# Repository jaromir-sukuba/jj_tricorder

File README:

This is repository for JJ Tricorder project, hosted here http://hackaday.io/project/521-JJ-Tricoder

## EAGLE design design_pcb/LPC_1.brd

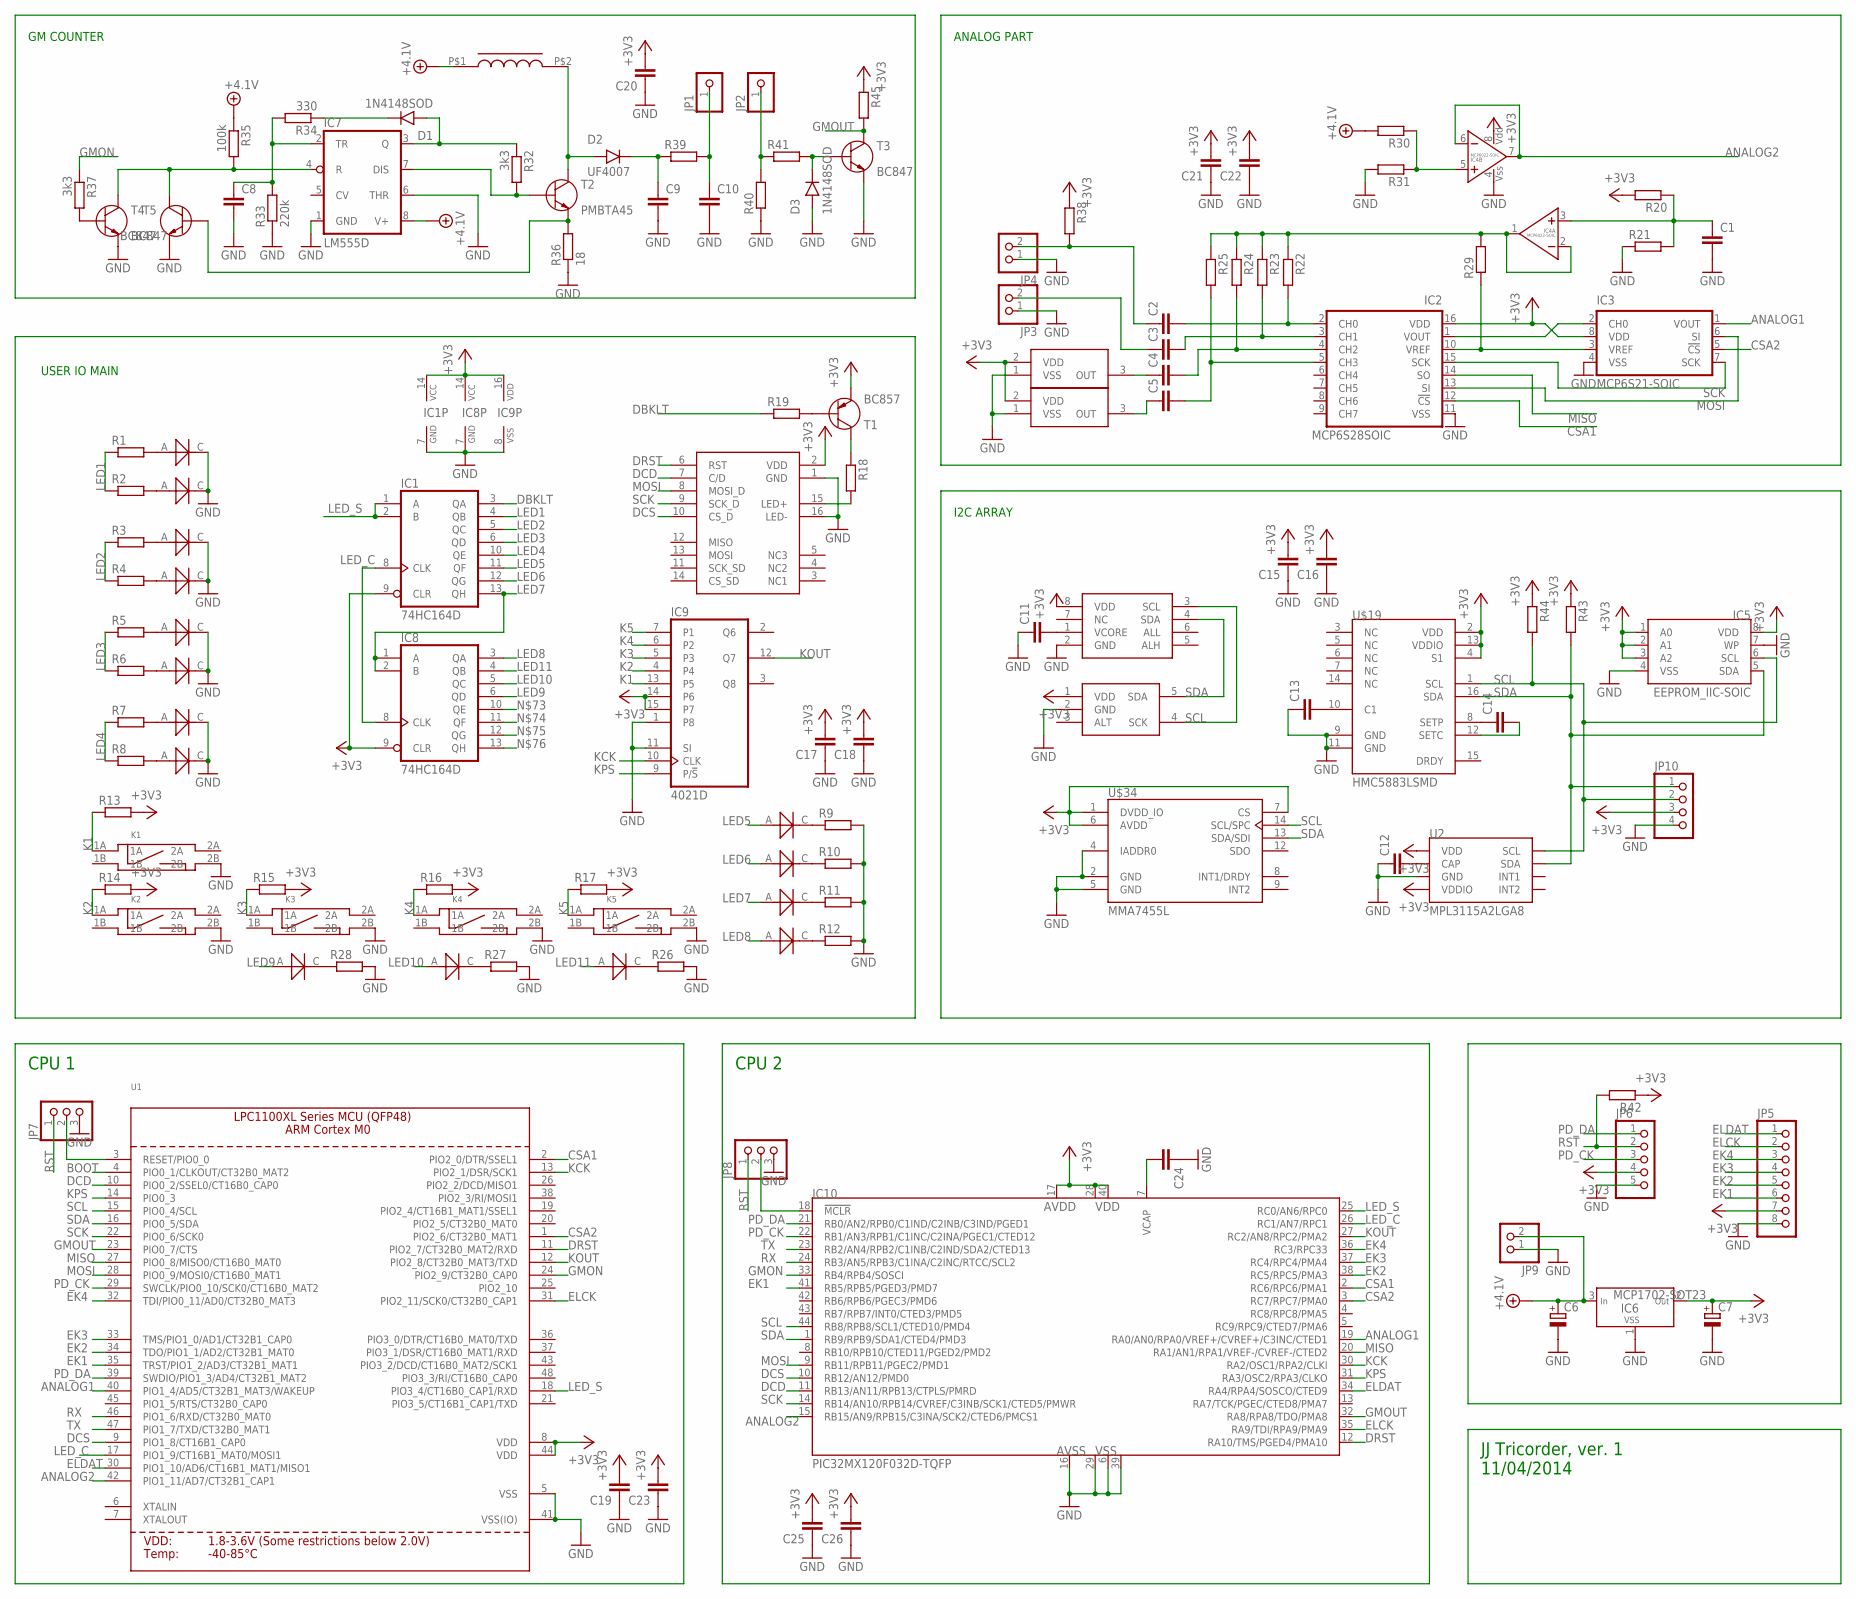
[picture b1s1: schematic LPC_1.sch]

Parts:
C1, C8, C11, C12, C13, C14, C15, C16, C17, C18, C19, C20, C21, C22, C23, C24, C25, C26: C_0806; R0805
C2, C3, C4, C5, C9, C10: C_1206; R1206
C6, C7: CPOL-EUSMCA; SMC_A
D1, D3: 1N4148SOD; SOD-80
D2: UF4007; SM-1
IC1, IC8: 74HC164D; SO14
IC2: MCP6S28SOIC; SO-16
IC3: MCP6S21-SOIC; SO-08
IC4: MCP6022-SOIC; SO-08
IC5: EEPROM_IIC-SOIC; SO-08
IC6: MCP1702-SOT23; SOT23
IC7: LM555D; SO08
IC9: 4021D; SO16
IC10: PIC32MX120F032D-TQFP; TQFP44
JP1, JP2: PINHD-1X1; 1X01
JP3, JP4: PINHD-1X02_2.54; 1X02
JP5: PINHD-1X08_2.54-S; 1X08-S
JP6: PINHD-1X05_2.54-90°-S; 1X05/90-S
JP7, JP8: PINHD-1X03_2.00; 1X03M
JP9: PINHD-1X02_2.54-90°; 1X02/90
JP10: PINHD-1X04_2.00; 1X04M
K1, K2, K3, K4, K5: SWITCH_BD_B; SW_SMD2
R1, R2, R3, R4, R5, R6, R7, R8, R9, R10, R11, R12, R13, R14, R15, R16, R17, R18, R19, R20, R21, R22, R23, R24, R25, R26, R27, R28, R29, R30, R31, R38, R41, R42, R43, R44, R45: R_0805; R0805
R32, R37: 3k3; R0805
R33: 220k; R0805
R34: 330; R0805
R35: 100k; R0805
R36: 18; R0805
R39, R40: R_1206; R1206
T1: BC857; SOT23
T2: PMBTA45; SOT23
T3, T4, T5: BC847; SOT23
U1: LPC1113/4/5_QFP48_XLSERIES; LQFP48
U2: MPL3115A2LGA8; LGA8
U$1, U$11, U$12, U$13, U$14, U$15, U$16: LED5X2; LED_5X2
U$2, U$4, U$5, U$6, U$7, U$8, U$9, U$10: LED5X5; LED_5X5
U$3: DISP_TFT_18; DSIP_TFT_18
U$17: HIH-6130; SO8
U$18: MCP9800; SOT23-5
U$19: HMC5883LSMD; 16LPCC
U$20: IND_DL22
U$21, U$22: TSL252
U$34: MMA7455L; LGA14

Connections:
+3V3: C7.+, C15.2, C16.2, C17.2, C18.2, C19.2, C20.2, C21.2, C22.2, C23.2, C25.2, C26.2, IC1.9 (CLR), IC1.14 (VCC), IC2.16 (VDD), IC3.8 (VDD), IC4.8 (VDD), IC5.1 (A0), IC5.2 (A1), IC5.3 (A2), IC5.8 (VDD), IC6.2 (OUT), IC8.9 (CLR), IC8.14 (VCC), IC9.14 (P6), IC9.15 (P7), IC9.16 (VDD), IC10.17 (AVDD), IC10.28 (VDD), IC10.40 (VDD2), JP5.7, JP6.4, JP10.3, R13.2, R14.2, R15.2, R16.2, R17.2, R20.2, R38.1, R42.1, R43.1, R44.1, R45.1, T1.3 (C), U1.8 (VDD), U1.44 (VDD), U2.1 (VDD), U2.4 (VDDIO), U$3.2 (VDD), U$17.8 (VDD), U$18.1 (VDD), U$19.2 (VDD), U$19.4 (S1), U$19.13 (VDDIO), U$21.2 (VDD), U$22.2 (VDD), U$34.1 (DVDD_IO), U$34.6 (AVDD), U$34.7 (CS)
+4.1V: C6.+, IC6.3 (IN), IC7.8 (V+), JP9.2, R30.2, R35.1, U$20.P$1
ANALOG1: IC3.1 (VOUT), IC10.19 (RA0/AN0/RPA0/VREF+/CVREF+/C3INC/CTED1), U1.40 (PIO1_4/AD5/CT32B1_MAT3/WAKEUP)
ANALOG2: IC4.6 (IN-), IC4.7 (VYSTUP), IC10.15 (RB15/AN9/RPB15/C3INA/SCK2/CTED6/PMCS1), U1.42 (PIO1_11/AD7/CT32B1_CAP1)
BOOT: U1.4 (PIO0_1/CLKOUT/CT32B0_MAT2)
CSA1: IC2.12 (!CS), IC10.2 (RC6/RPC6/PMA1), U1.2 (PIO2_0/DTR/SSEL1)
CSA2: IC3.5 (!CS), IC10.3 (RC7/RPC7/PMA0), U1.1 (PIO2_6/CT32B0_MAT1)
DBKLT: IC1.3 (QA), R19.1
DCD: IC10.11 (RB13/AN11/RPB13/CTPLS/PMRD), U1.10 (PIO0_2/SSEL0/CT16B0_CAP0), U$3.7 (C/D)
DCS: IC10.10 (RB12/AN12/PMD0), U1.9 (PIO1_8/CT16B1_CAP0), U$3.10 (CS_D)
DRST: IC10.12 (RA10/TMS/PGED4/PMA10), U1.11 (PIO2_7/CT32B0_MAT2/RXD), U$3.6 (RST)
EK1: IC10.41 (RB5/RPB5/PGED3/PMD7), JP5.6, U1.35 (TRST/PIO1_2/AD3/CT32B1_MAT1)
EK2: IC10.38 (RC5/RPC5/PMA3), JP5.5, U1.34 (TDO/PIO1_1/AD2/CT32B1_MAT0)
EK3: IC10.37 (RC4/RPC4/PMA4), JP5.4, U1.33 (TMS/PIO1_0/AD1/CT32B1_CAP0)
EK4: IC10.36 (RC3/RPC33), JP5.3, U1.32 (TDI/PIO0_11/AD0/CT32B0_MAT3)
ELCK: IC10.35 (RA9/TDI/RPA9/PMA9), JP5.2, U1.31 (PIO2_11/SCK0/CT32B0_CAP1)
ELDAT: IC10.34 (RA4/RPA4/SOSCO/CTED9), JP5.1, U1.30 (PIO1_10/AD6/CT16B1_MAT1/MISO1)
GMON: IC10.33 (RB4/RPB4/SOSCI), R37.1, U1.24 (PIO2_9/CT32B0_CAP0)
GMOUT: IC10.32 (RA8/RPA8/TDO/PMA8), R45.2, T3.3 (C), U1.23 (PIO0_7/CTS)
GND: C1.2, C6.-, C7.-, C8.2, C9.2, C10.2, C11.1, C12.1, C13.1, C15.1, C16.1, C17.1, C18.1, C19.1, C20.1, C21.1, C22.1, C23.1, C24.1, C25.1, C26.1, D3.A, IC1.7 (GND), IC2.11 (VSS), IC3.4 (VSS), IC4.4 (VSS), IC5.4 (VSS), IC5.7 (WP), IC6.1 (VSS), IC7.1 (GND), IC7.6 (THR), IC8.7 (GND), IC9.1 (P8), IC9.8 (VSS), IC9.11 (SI), IC10.6 (VSS1), IC10.16 (AVSS), IC10.29 (VSS), IC10.39 (VSS2), JP3.1, JP4.1, JP5.8, JP6.5, JP7.3, JP8.3, JP9.1, JP10.4, K1.2B, K2.2B, K3.2B, K4.2B, K5.2B, R9.2, R10.2, R11.2, R12.2, R21.1, R26.2, R27.2, R28.2, R31.2, R33.1, R36.1, R40.1, T3.2 (E), T4.2 (E), T5.2 (E), U1.5 (VSS), U1.41 (VSS(IO)), U2.3 (GND), U$2.C, U$3.1 (GND), U$3.16 (LED-), U$4.C, U$5.C, U$6.C, U$7.C, U$8.C, U$9.C, U$10.C, U$17.2 (GND), U$18.2 (GND), U$19.9 (GND), U$19.11 (GND), U$21.1 (VSS), U$22.1 (VSS), U$34.2 (GND), U$34.4 (IADDR0), U$34.5 (GND)
K1: IC9.13 (P5), K1.1A, R13.1
K2: IC9.4, K2.1A, R14.1
K3: IC9.5 (P3), K3.1A, R15.1
K4: IC9.6 (P2), K4.1A, R16.1
K5: IC9.7 (P1), K5.1A, R17.1
KCK: IC9.10 (CLK), IC10.30 (RA2/OSC1/RPA2/CLKI), U1.13 (PIO2_1/DSR/SCK1)
KOUT: IC9.12 (Q7), IC10.27 (RC2/AN8/RPC2/PMA2), U1.12 (PIO2_8/CT32B0_MAT3/TXD)
KPS: IC9.9 (P/!S), IC10.31 (RA3/OSC2/RPA3/CLKO), U1.14 (PIO0_3)
LED1: IC1.4 (QB), R1.1, R2.1
LED2: IC1.5 (QC), R3.1, R4.1
LED3: IC1.6 (QD), R5.1, R6.1
LED4: IC1.10 (QE), R7.1, R8.1
LED5: IC1.11 (QF), U$13.A
LED6: IC1.12 (QG), U$1.A
LED7: IC1.13 (QH), IC8.1 (A), IC8.2 (B), U$11.A
LED8: IC8.3 (QA), U$12.A
LED9: IC8.6 (QD), U$16.A
LED10: IC8.5 (QC), U$15.A
LED11: IC8.4 (QB), U$14.A
LED_C: IC1.8 (CLK), IC8.8 (CLK), IC10.26 (RC1/AN7/RPC1), U1.17 (PIO1_9/CT16B1_MAT0/MOSI1)
LED_S: IC1.1 (A), IC1.2 (B), IC10.25 (RC0/AN6/RPC0), U1.18 (PIO3_4/CT16B0_CAP1/RXD)
MISO: IC2.14 (SO), IC10.20 (RA1/AN1/RPA1/VREF-/CVREF-/CTED2), U1.27 (PIO0_8/MISO0/CT16B0_MAT0)
MOSI: IC2.13 (SI), IC3.6 (SI), IC10.9 (RB11/RPB11/PGEC2/PMD1), U1.28 (PIO0_9/MOSI0/CT16B0_MAT1), U$3.8 (MOSI_D)
unnamed: R1.2, U$2.A
unnamed: R2.2, U$4.A
unnamed: IC2.10 (VREF), IC3.3 (VREF), R29.1
unnamed: R3.2, U$5.A
unnamed: R4.2, U$6.A
unnamed: C1.1, IC4.3 (NEIN+), R20.1, R21.2
unnamed: IC2.1 (VOUT), IC3.2 (CH0)
unnamed: R5.2, U$7.A
unnamed: R6.2, U$8.A
unnamed: R26.1, U$14.C
unnamed: R18.2, U$3.15 (LED+)
unnamed: R7.2, U$9.A
unnamed: R8.2, U$10.A
unnamed: R18.1, T1.2 (E)
unnamed: R19.2, T1.1 (B)
unnamed: R9.1, U$13.C
unnamed: R10.1, U$1.C
unnamed: R11.1, U$11.C
unnamed: R12.1, U$12.C
unnamed: C2.2, IC2.2 (CH0), R22.2
unnamed: C3.2, IC2.3 (CH1), R23.2
unnamed: C4.2, IC2.4 (CH2), R24.2
unnamed: C5.2, IC2.5 (CH3), R25.2
unnamed: R27.1, U$15.C
unnamed: R28.1, U$16.C
unnamed: IC4.1 (VYSTUP), IC4.2 (IN-), R22.1, R23.1, R24.1, R25.1, R29.2
unnamed: IC4.5 (NEIN+), R30.1, R31.1
unnamed: D1.K, R34.1
unnamed: D1.A, IC7.3 (Q), R32.1
unnamed: IC7.7 (DIS), R32.2, T2.1 (B)
unnamed: IC7.4 (R), R35.2, T4.3 (C), T5.3 (C)
unnamed: C8.1, IC7.2 (TR), R33.2, R34.2
unnamed: R37.2, T4.1 (B)
unnamed: C9.1, D2.K, R39.1
unnamed: C10.1, JP1.1, R39.2
unnamed: D2.A, T2.3 (C), U$20.P$2
unnamed: JP2.1, R40.2, R41.1
unnamed: D3.K, R41.2, T3.1 (B)
unnamed: R36.2, T2.2 (E), T5.1 (B)
unnamed: C11.2, U$17.1 (VCORE)
unnamed: C24.2, IC10.7 (VCAP)
unnamed: JP7.2, U1.3 (RESET/PIO0_0)
unnamed: C12.2, U2.2 (CAP)
unnamed: C13.2, U$19.10 (C1)
unnamed: C14.1, U$19.8 (SETP)
unnamed: C14.2, U$19.12 (SETC)
unnamed: C5.1, U$21.3 (OUT)
unnamed: C4.1, U$22.3 (OUT)
unnamed: IC10.18 (!MCLR), JP8.2
unnamed: C3.1, JP3.2
unnamed: C2.1, JP4.2, R38.2
PD_CK: IC10.22 (RB1/AN3/RPB1/C1INC/C2INA/PGEC1/CTED12), JP6.3, U1.29 (SWCLK/PIO0_10/SCK0/CT16B0_MAT2)
PD_DA: IC10.21 (RB0/AN2/RPB0/C1IND/C2INB/C3IND/PGED1), JP6.1, U1.39 (SWDIO/PIO1_3/AD4/CT32B1_MAT2)
RST: JP6.2, JP7.1, JP8.1, R42.2
RX: IC10.24 (RB3/AN5/RPB3/C1INA/C2INC/RTCC/SCL2), U1.46 (PIO1_6/RXD/CT32B0_MAT0)
SCK: IC2.15 (SCK), IC3.7 (SCK), IC10.14 (RB14/AN10/RPB14/CVREF/C3INB/SCK1/CTED5/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), U1.22 (PIO0_6/SCK0), U$3.9 (SCK_D)
SCL: IC5.6 (SCL), IC10.44 (RB8/RPB8/SCL1/CTED10/PMD4), JP10.2, R44.2, U1.15 (PIO0_4/SCL), U2.8 (SCL), U$17.3 (SCL), U$18.4 (SCK), U$19.1 (SCL), U$34.14 (SCL/SPC)
SDA: IC5.5 (SDA), IC10.1 (RB9/RPB9/SDA1/CTED4/PMD3), JP10.1, R43.2, U1.16 (PIO0_5/SDA), U2.7 (SDA), U$17.4 (SDA), U$18.5 (SDA), U$19.16 (SDA), U$34.13 (SDA/SDI)
TX: IC10.23 (RB2/AN4/RPB2/C1INB/C2IND/SDA2/CTED13), U1.47 (PIO1_7/TXD/CT32B0_MAT1)

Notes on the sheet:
ANALOG PART
I2C ARRAY
USER IO MAIN
GM COUNTER
JJ Tricorder, ver. 1 11/04/2014
CPU 1
CPU 2

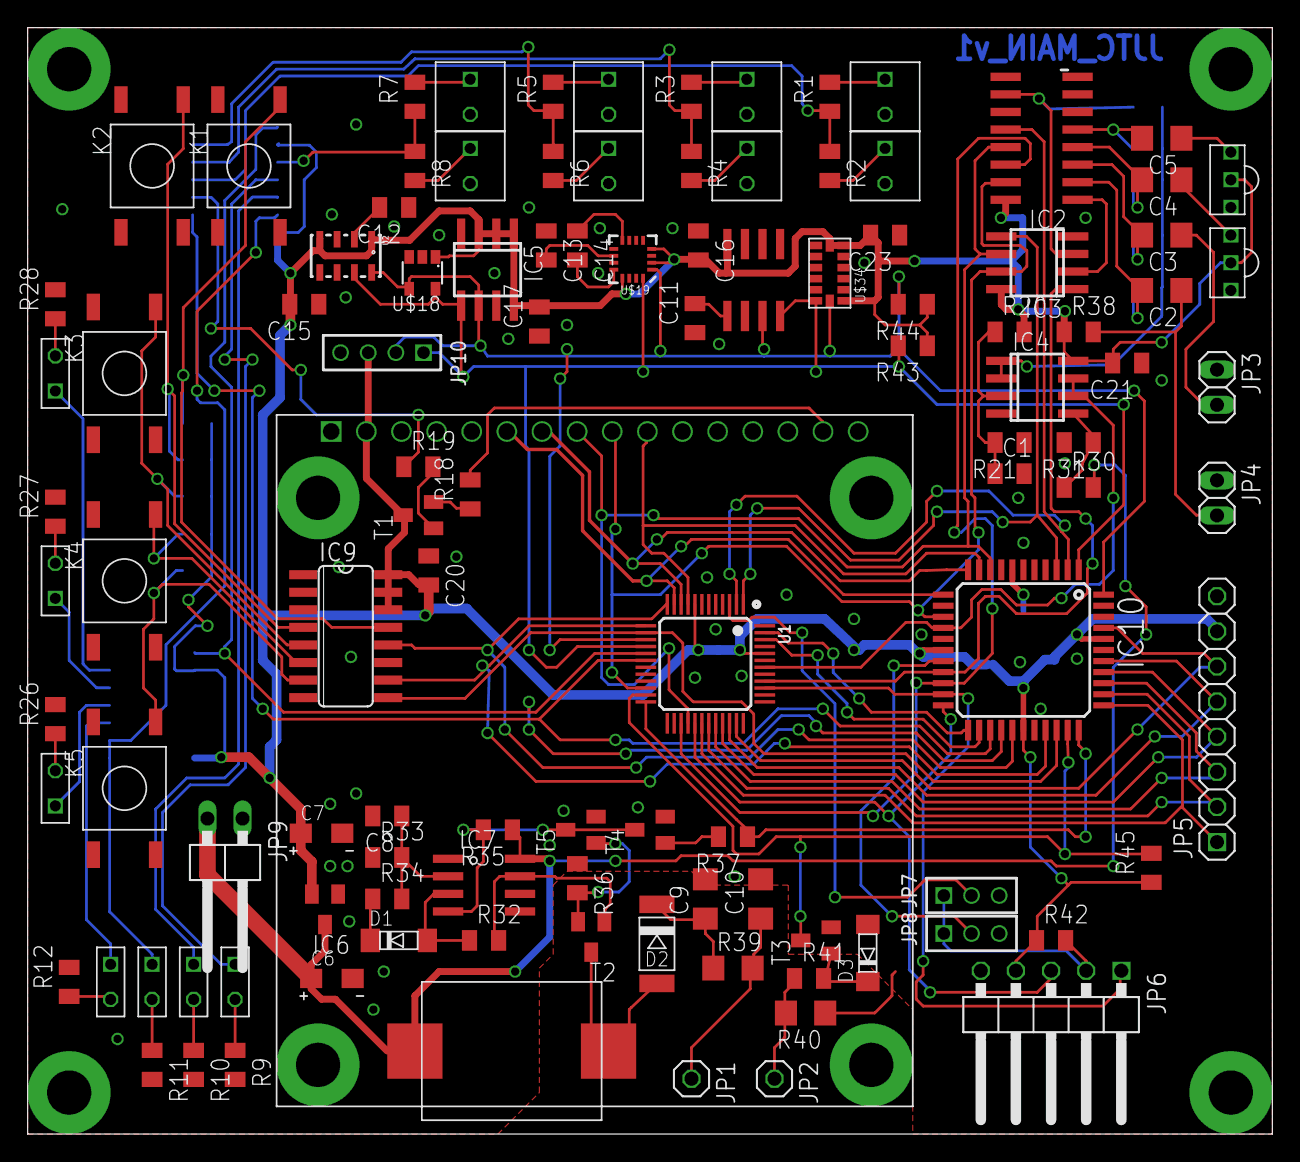
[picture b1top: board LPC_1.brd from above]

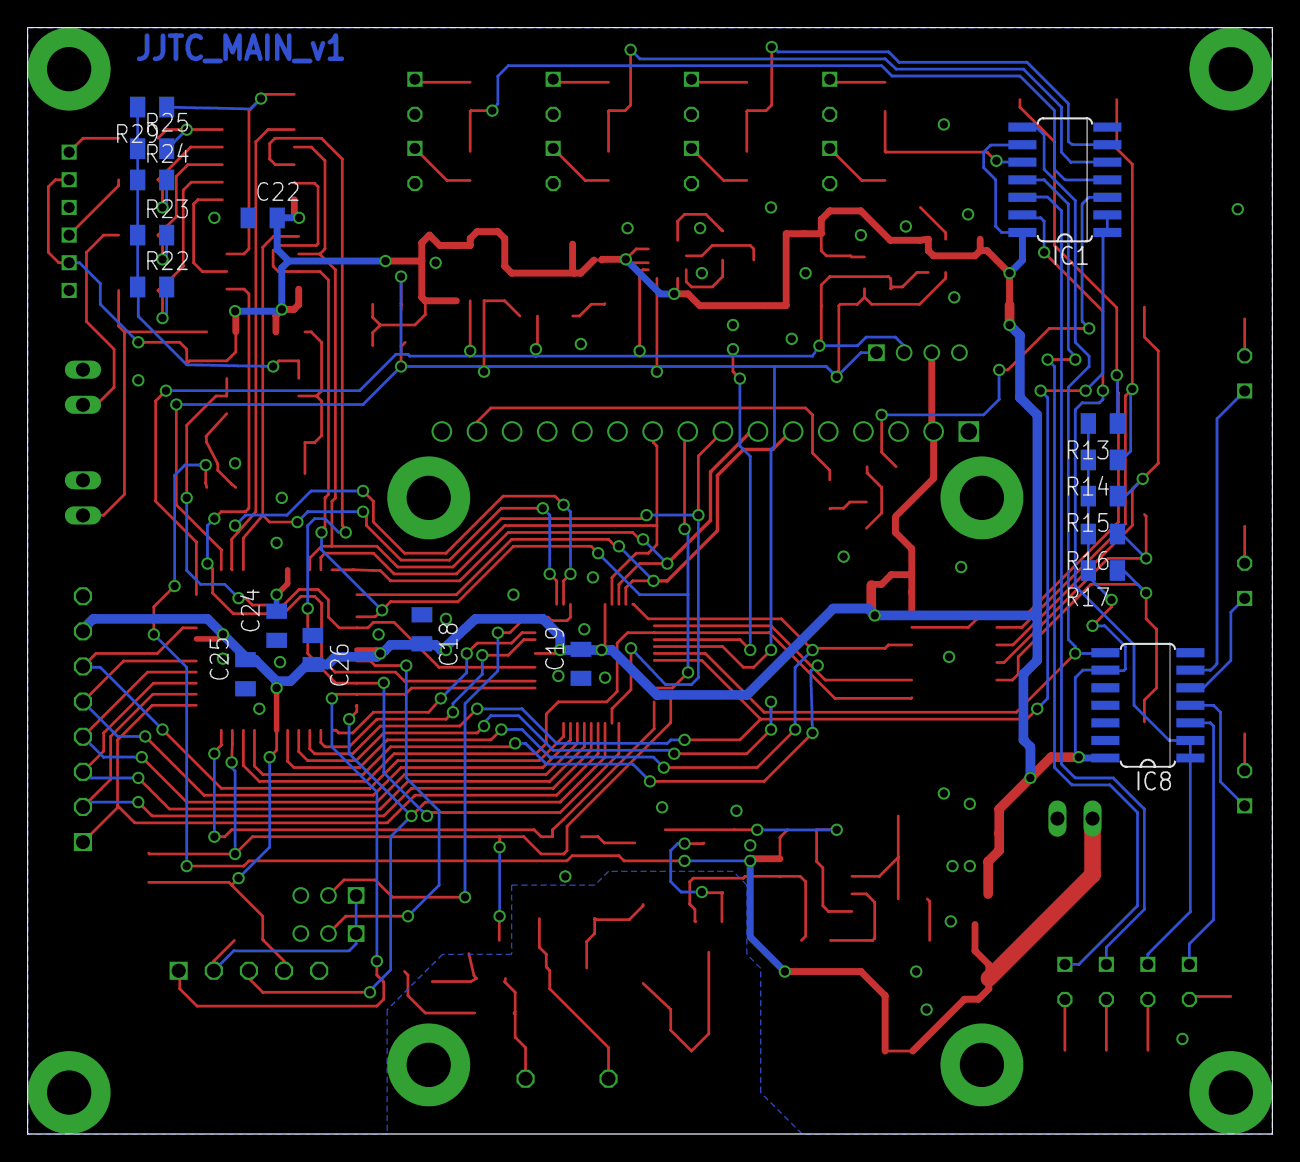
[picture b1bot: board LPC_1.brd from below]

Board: 2 copper layers, 90.0 x 80.0 mm, 129 parts (18 on the bottom side), 101 nets.

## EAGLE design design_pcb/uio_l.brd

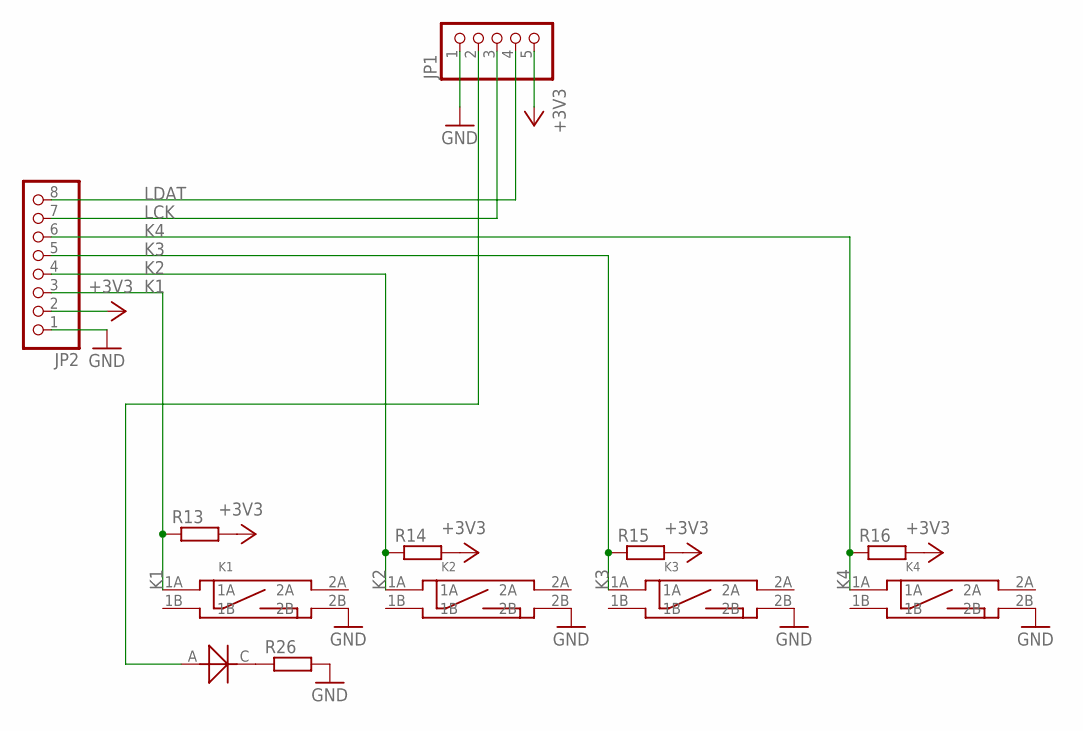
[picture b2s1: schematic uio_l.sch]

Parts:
JP1: PINHD-1X05_2.54-S; 1X05-S
JP2: PINHD-1X08_2.54-S; 1X08-S
K1, K2, K3, K4: SWITCH_BD_B; SW_SMD2
R13, R14, R15, R16, R26: R_0805; R0805
U$14: LED5X2; LED_5X2

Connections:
+3V3: JP1.5, JP2.2, R13.2, R14.2, R15.2, R16.2
GND: JP1.1, JP2.1, K1.2B, K2.2B, K3.2B, K4.2B, R26.2
K1: JP2.3, K1.1A, R13.1
K2: JP2.4, K2.1A, R14.1
K3: JP2.5, K3.1A, R15.1
K4: JP2.6, K4.1A, R16.1
LCK: JP1.3, JP2.7
LDAT: JP1.4, JP2.8
LED11: JP1.2, U$14.A
unnamed: R26.1, U$14.C

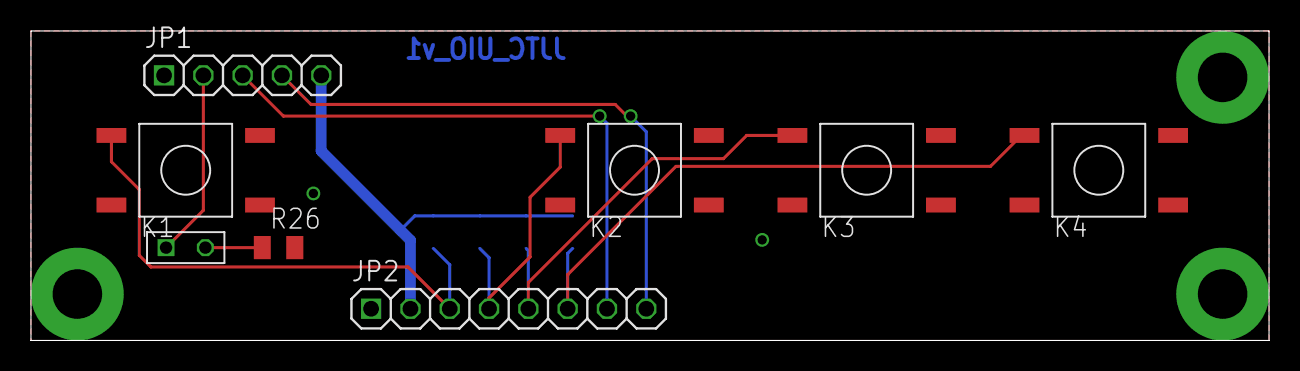
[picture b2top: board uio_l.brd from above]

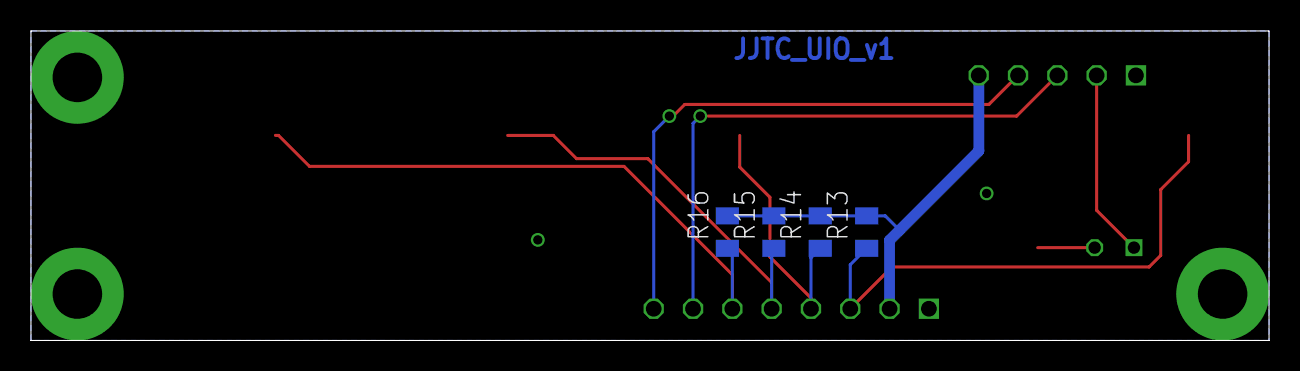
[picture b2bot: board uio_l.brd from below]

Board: 2 copper layers, 80.0 x 20.0 mm, 12 parts (4 on the bottom side), 10 nets.

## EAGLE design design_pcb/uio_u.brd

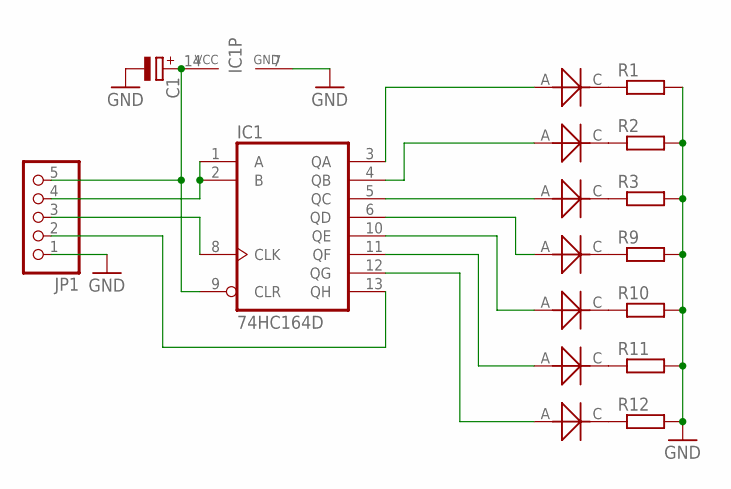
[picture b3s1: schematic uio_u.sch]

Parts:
C1: CPOL-EUSMCA; SMC_A
IC1: 74HC164D; SO14
JP1: PINHD-1X05_2.54-S; 1X05-S
R1, R2, R3, R9, R10, R11, R12: R_0805; R0805
U$1, U$2, U$3, U$4, U$11, U$12, U$13: LED5X2; LED_5X2

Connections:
GND: C1.-, IC1.7 (GND), JP1.1, R1.2, R2.2, R3.2, R9.2, R10.2, R11.2, R12.2
LED1: IC1.3 (QA), U$4.A
LED2: IC1.4 (QB), U$2.A
LED3: IC1.5 (QC), U$3.A
LED5: IC1.6 (QD), U$13.A
LED6: IC1.10 (QE), U$1.A
LED7: IC1.11 (QF), U$11.A
LED8: IC1.12 (QG), U$12.A
unnamed: R1.1, U$4.C
unnamed: R2.1, U$2.C
unnamed: R3.1, U$3.C
unnamed: IC1.13 (QH), JP1.2
unnamed: IC1.8 (CLK), JP1.3
unnamed: IC1.1 (A), IC1.2 (B), JP1.4
unnamed: C1.+, IC1.9 (CLR), IC1.14 (VCC), JP1.5
unnamed: R9.1, U$13.C
unnamed: R10.1, U$1.C
unnamed: R11.1, U$11.C
unnamed: R12.1, U$12.C

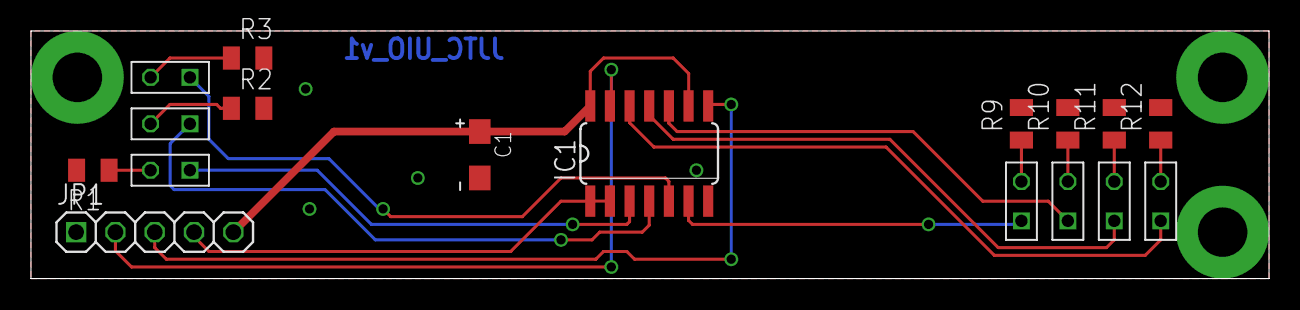
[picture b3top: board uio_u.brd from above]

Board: 2 copper layers, 80.0 x 16.0 mm, 17 parts (0 on the bottom side), 19 nets.

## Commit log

2014-04-22 rev 1
2014-04-29 sources v1
2014-04-29 3D files, v1
2014-04-29 LPC 1114 sources

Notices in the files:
parts and their libraries:
microbuilder: This work is placed in the public domain, and may be freely used for commercial and non-commercial work with the following conditions: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
SparkFun-Sensors: Licensing: CC v3.0 Share-Alike You are welcome to use this library for commercial purposes.
